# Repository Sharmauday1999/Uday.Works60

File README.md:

# Uday.Works60
 PCB for the FILO60

Features:
- Supports Gasket Mount Boards
- JST connector
- Underglow and in-switch LEDs
- GH60 Layout
- ESD and Over-current protection
- I don't remember the rest :/

It is an Autodesk Eagle Project, I don't have all the footprints handy, but a bit of google should have you set up in no time! I am currently testing a prototype for this but in no way do I guarantee its functionality. This was the biggest PCB project I have ever done and I learned quite alot, feel free to contribute!

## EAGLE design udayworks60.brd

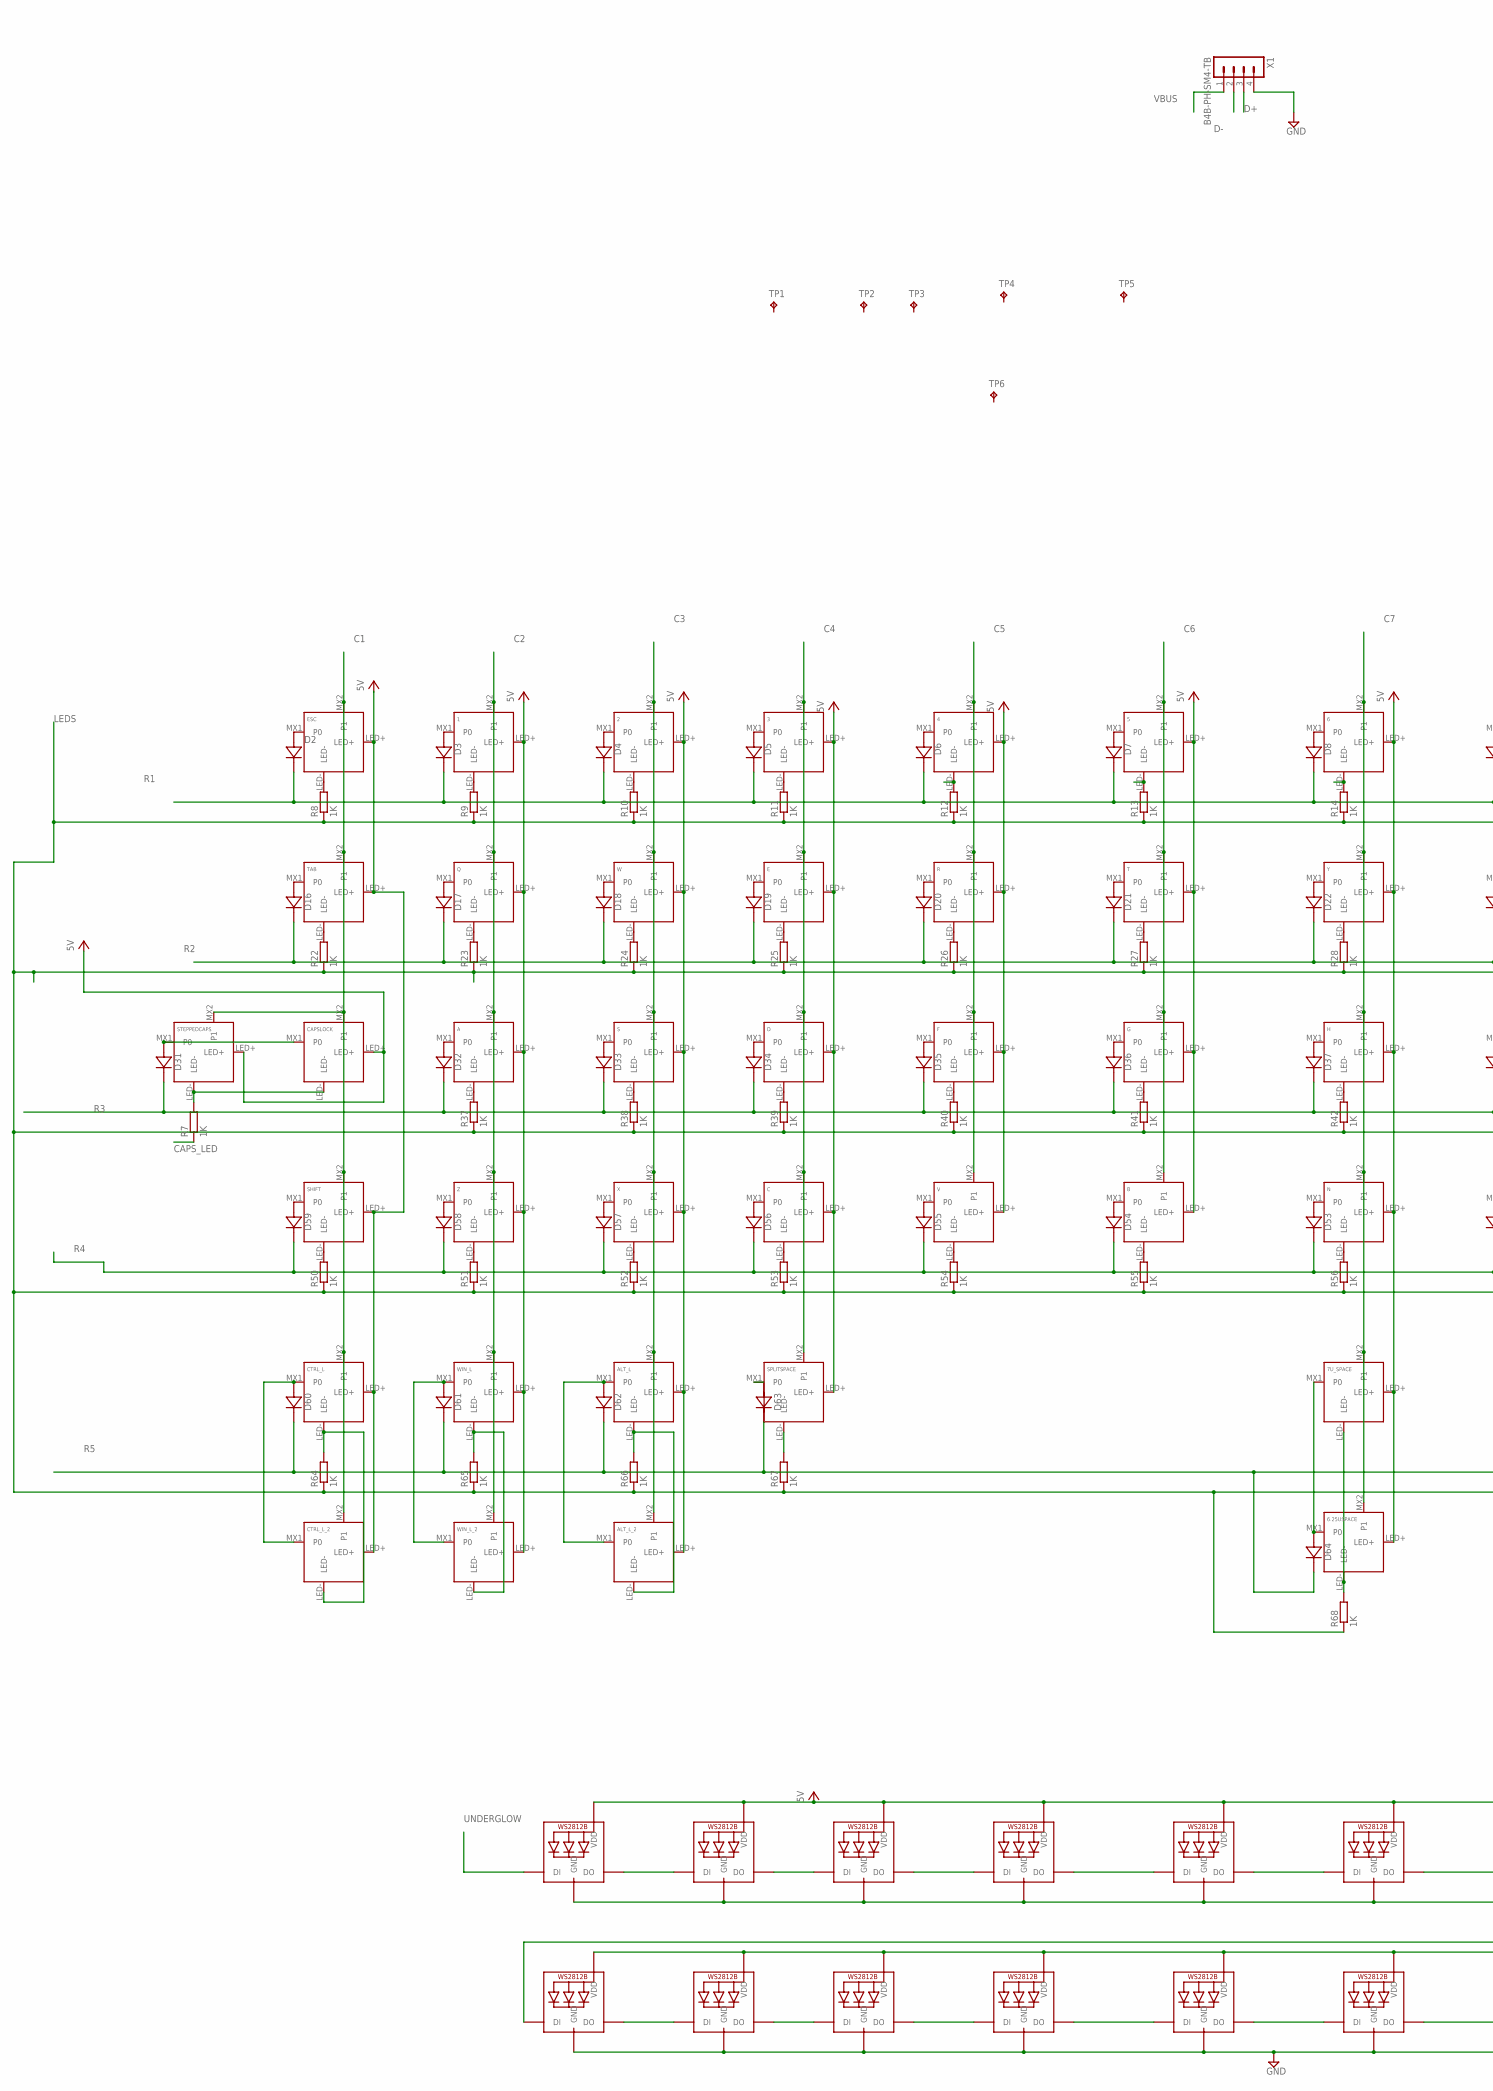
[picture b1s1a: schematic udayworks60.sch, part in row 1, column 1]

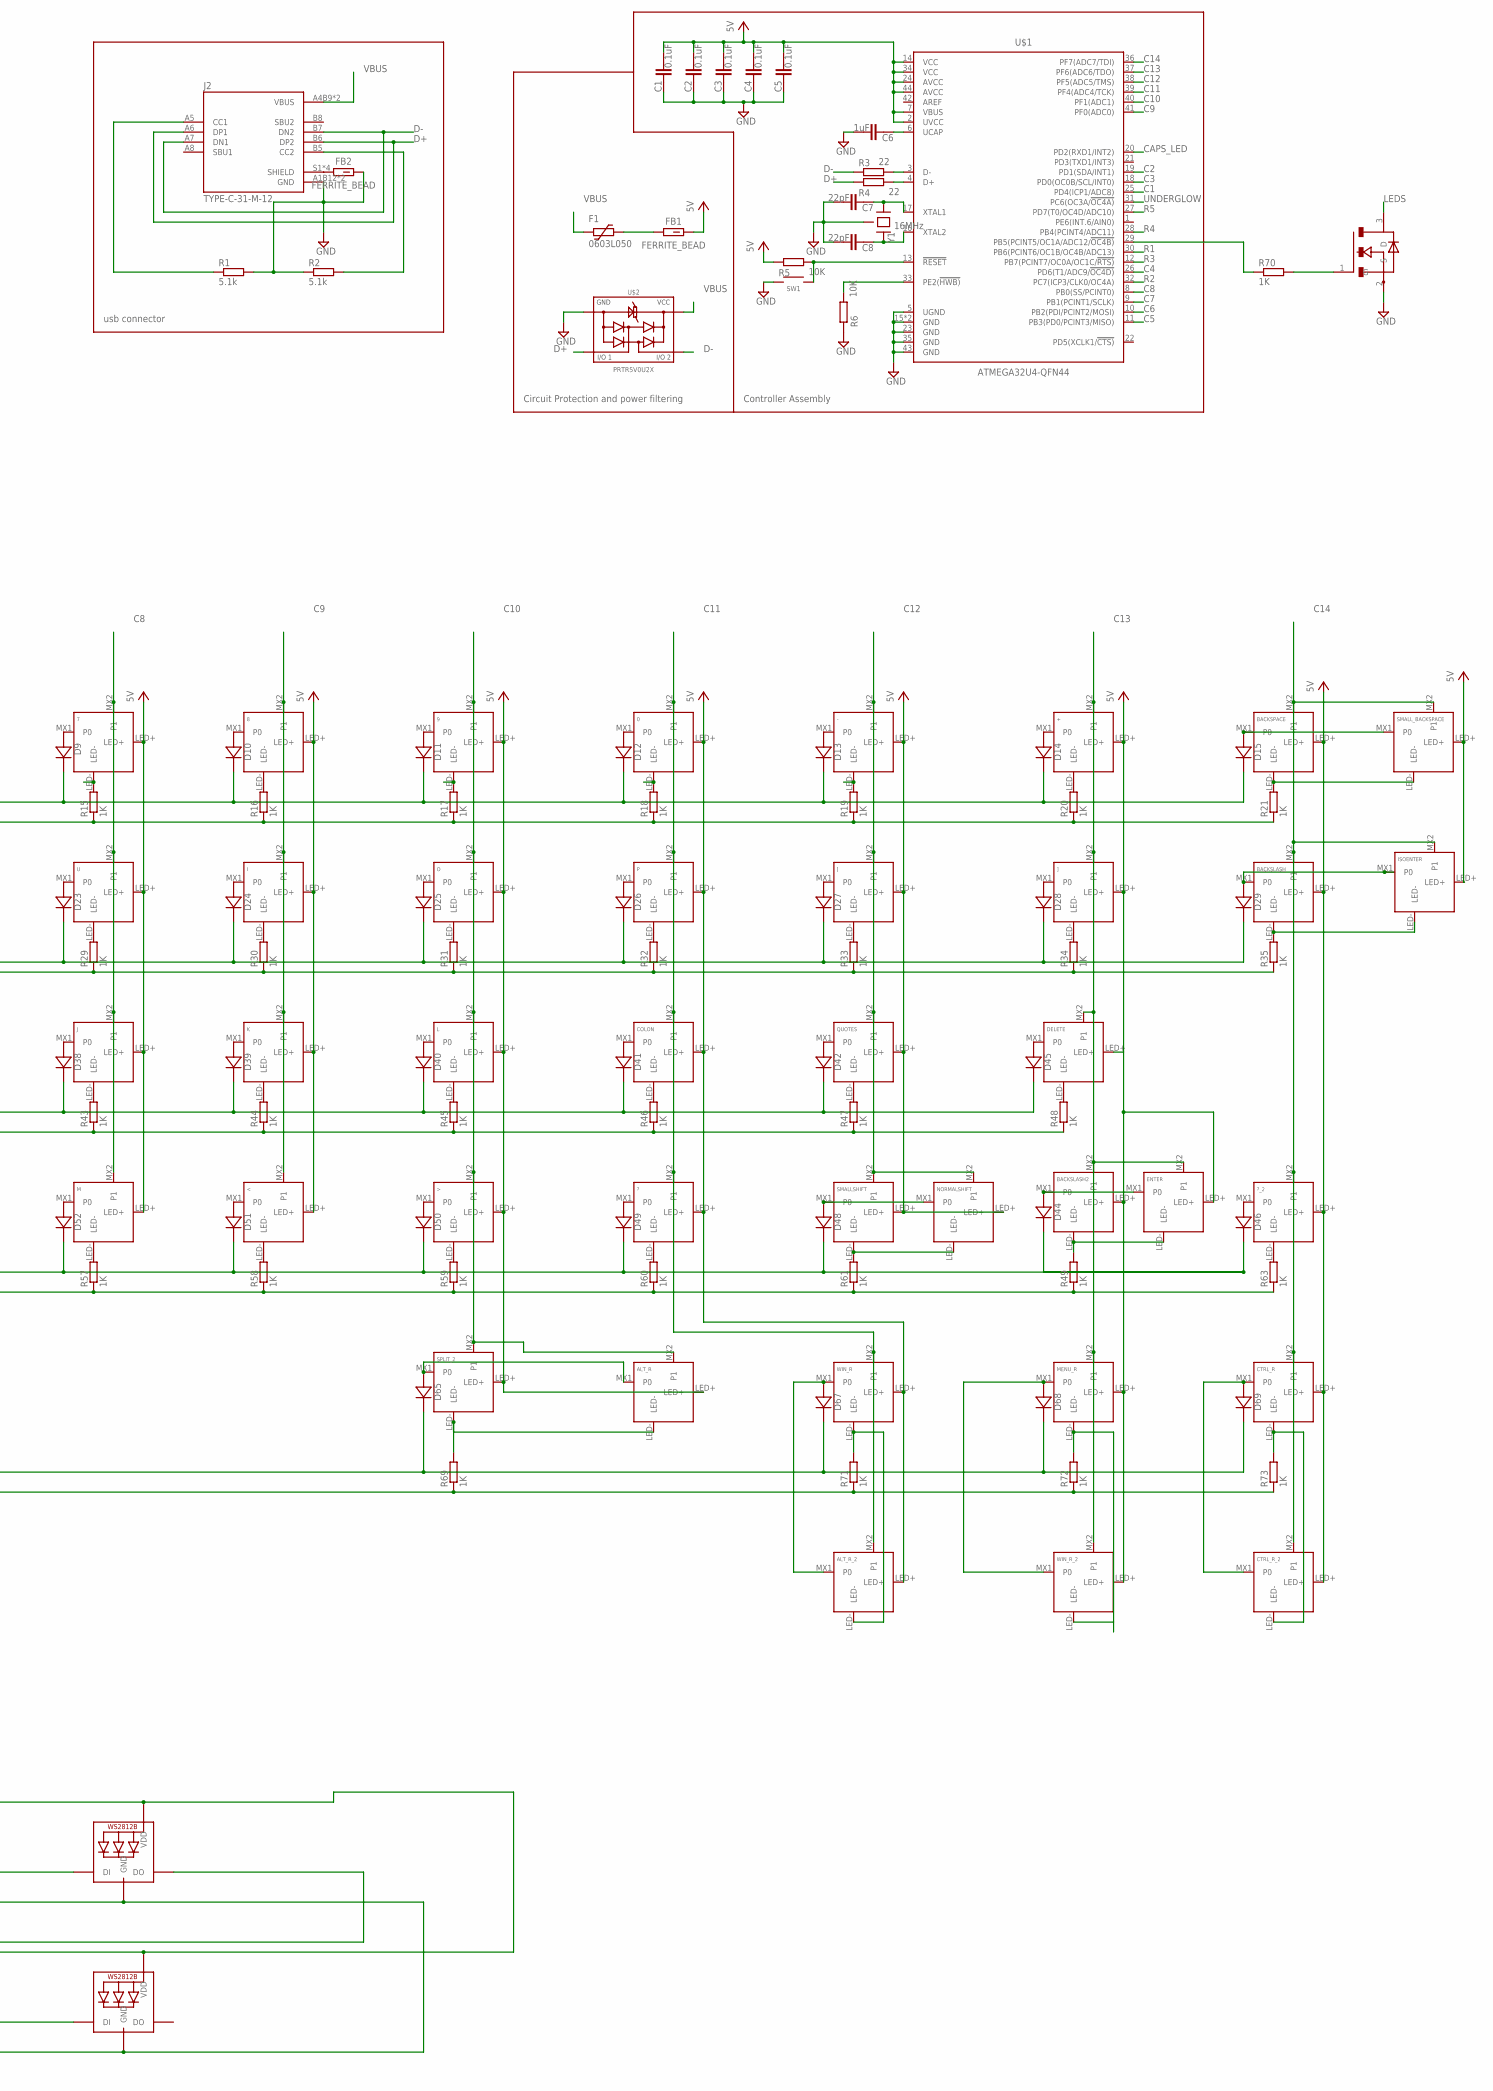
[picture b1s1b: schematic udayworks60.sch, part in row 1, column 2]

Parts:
0, 1, 2, 3, 4, 5, 6, 7, 8, 9: KEYSWITCH-LED-MX-1U-LED; MX-1U-LED
6.25USPACE: KEYSWITCH-LED-MX-6.25U-LED-FLIPPED; MX-6.25U-LED-FLIPPED
7U_SPACE: KEYSWITCH-LED-MX-7U-LED-FLIPPED; MX-7U-LED-FLIPPED
+: KEYSWITCH-LED-MX-1U-LED; MX-1U-LED
-: KEYSWITCH-LED-MX-1U-LED; MX-1U-LED
<: KEYSWITCH-LED-MX-1U-LED; MX-1U-LED
>: KEYSWITCH-LED-MX-1U-LED; MX-1U-LED
?: KEYSWITCH-LED-MX-1U-LED; MX-1U-LED
?_2: KEYSWITCH-LED-MX-1U-LED; MX-1U-LED
A: KEYSWITCH-LED-MX-1U-LED; MX-1U-LED
ALT_L: KEYSWITCH-LED-MX-1U-LED; MX-1U-LED
ALT_L_2: KEYSWITCH-LED-MX-1U-LED; MX-1U-LED
ALT_R: KEYSWITCH-LED-MX-1U-LED; MX-1U-LED
ALT_R_2: KEYSWITCH-LED-MX-1U-LED; MX-1U-LED
B: KEYSWITCH-LED-MX-1U-LED; MX-1U-LED
BACKSLASH, BACKSLASH2: KEYSWITCH-LED-MX-1U-LED; MX-1U-LED
BACKSPACE: KEYSWITCH-LED-MX-2U-LED; MX-2U-LED
C: KEYSWITCH-LED-MX-1U-LED; MX-1U-LED
C1, C2, C3, C4, C5: 0.1uF; C0603
C6: 1uF; C0603
C7, C8: 22pF; C0603
CAPSLOCK: KEYSWITCH-LED-MX-1U-LED; MX-1U-LED
COLON: KEYSWITCH-LED-MX-1U-LED; MX-1U-LED
CTRL_L: KEYSWITCH-LED-MX-1U-LED; MX-1U-LED
CTRL_L_2: KEYSWITCH-LED-MX-1U-LED; MX-1U-LED
CTRL_R: KEYSWITCH-LED-MX-1U-LED; MX-1U-LED
CTRL_R_2: KEYSWITCH-LED-MX-1U-LED; MX-1U-LED
D: KEYSWITCH-LED-MX-1U-LED; MX-1U-LED
D2, D3, D4, D5, D6, D7, D8, D9, D10, D11, D12, D13, D14, D15, D16, D17, D18, D19, D20, D21, D22, D23, D24, D25, D26, D27, D28, D29, D31, D32, D33, D34, D35, D36, D37, D38, D39, D40, D41, D42, D44, D45, D46, D48, D49, D50, D51, D52, D53, D54, D55, D56, D57, D58, D59, D60, D61, D62, D63, D64, D65, D67, D68, D69: DIODE-SOD-123; SOD-123
DELETE: KEYSWITCH-LED-MX-1U-LED; MX-1U-LED
E: KEYSWITCH-LED-MX-1U-LED; MX-1U-LED
ENTER: KEYSWITCH-LED-MX-2U-LED; MX-2U-LED
ESC: KEYSWITCH-LED-MX-1U-LED; MX-1U-LED
F: KEYSWITCH-LED-MX-1U-LED; MX-1U-LED
F1: 0603L050; 0603L
FB1, FB2: FERRITE_BEAD; BEADC1608X95N
FET1: FET-SOT-23-3; SOT-23-3
G: KEYSWITCH-LED-MX-1U-LED; MX-1U-LED
H: KEYSWITCH-LED-MX-1U-LED; MX-1U-LED
I: KEYSWITCH-LED-MX-1U-LED; MX-1U-LED
ISOENTER: KEYSWITCH-LED-MX-2U-LED-FLIPPED-ROTATED; MX-2U-LED-FLIPPED-ROTATED
J: KEYSWITCH-LED-MX-1U-LED; MX-1U-LED
J2: TYPE-C-31-M-12; HRO_TYPE-C-31-M-12
K: KEYSWITCH-LED-MX-1U-LED; MX-1U-LED
L: KEYSWITCH-LED-MX-1U-LED; MX-1U-LED
LED1, LED2, LED3, LED4, LED5, LED6, LED7, LED9, LED10, LED11, LED12, LED13, LED14, LED15: WS2812B3535; LED3535
M: KEYSWITCH-LED-MX-1U-LED; MX-1U-LED
MENU_R: KEYSWITCH-LED-MX-1U-LED; MX-1U-LED
N: KEYSWITCH-LED-MX-1U-LED; MX-1U-LED
NORMALSHIFT: KEYSWITCH-LED-MX-2U-LED; MX-2U-LED
O: KEYSWITCH-LED-MX-1U-LED; MX-1U-LED
P: KEYSWITCH-LED-MX-1U-LED; MX-1U-LED
Q: KEYSWITCH-LED-MX-1U-LED; MX-1U-LED
QUOTES: KEYSWITCH-LED-MX-1U-LED; MX-1U-LED
R: KEYSWITCH-LED-MX-1U-LED; MX-1U-LED
R1, R2: 5.1k; R0603
R3, R4: 22; R0603
R5, R6: 10K; R0603
R7, R8, R9, R10, R11, R12, R13, R14, R15, R16, R17, R18, R19, R20, R21, R22, R23, R24, R25, R26, R27, R28, R29, R30, R31, R32, R33, R34, R35, R37, R38, R39, R40, R41, R42, R43, R44, R45, R46, R47, R48, R49, R50, R51, R52, R53, R54, R55, R56, R57, R58, R59, R60, R61, R63, R64, R65, R66, R67, R68, R69, R70, R71, R72, R73: 1K; R0603
S: KEYSWITCH-LED-MX-1U-LED; MX-1U-LED
SHIFT: KEYSWITCH-LED-MX-2U-LED; MX-2U-LED
SMALLSHIFT: KEYSWITCH-LED-MX-1U-LED; MX-1U-LED
SMALL_BACKSPACE: KEYSWITCH-LED-MX-1U-LED; MX-1U-LED
SPLITSPACE: KEYSWITCH-LED-MX-2U-LED-FLIPPED; MX-2U-LED-FLIPPED
SPLIT_2: KEYSWITCH-LED-MX-2U-LED-FLIPPED; MX-2U-LED-FLIPPED
STEPPEDCAPS: KEYSWITCH-LED-MX-1U-LED; MX-1U-LED
SW1: SWITCH-SMD-EVP-BB2A9B00
T: KEYSWITCH-LED-MX-1U-LED; MX-1U-LED
TAB: KEYSWITCH-LED-MX-1U-LED; MX-1U-LED
TP1, TP2, TP3, TP4, TP5, TP6: TPPAD1-17Y; P1-17Y
U: KEYSWITCH-LED-MX-1U-LED; MX-1U-LED
U$1: ATMEGA32U4-QFN44; QFN-44
U$2: PRTR5V0U2X
V: KEYSWITCH-LED-MX-1U-LED; MX-1U-LED
W: KEYSWITCH-LED-MX-1U-LED; MX-1U-LED
WIN_L: KEYSWITCH-LED-MX-1U-LED; MX-1U-LED
WIN_L_2: KEYSWITCH-LED-MX-1U-LED; MX-1U-LED
WIN_R: KEYSWITCH-LED-MX-1U-LED; MX-1U-LED
WIN_R_2: KEYSWITCH-LED-MX-1U-LED; MX-1U-LED
X: KEYSWITCH-LED-MX-1U-LED; MX-1U-LED
X1: B4B-PH-SM4-TB
Y: KEYSWITCH-LED-MX-1U-LED; MX-1U-LED
Y1: 16MHz; CRYSTAL-3.2X2.5
Z: KEYSWITCH-LED-MX-1U-LED; MX-1U-LED
[: KEYSWITCH-LED-MX-1U-LED; MX-1U-LED
]: KEYSWITCH-LED-MX-1U-LED; MX-1U-LED

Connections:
C1: CAPSLOCK.MX2 (P1), CTRL_L.MX2 (P1), CTRL_L_2.MX2 (P1), ESC.MX2 (P1), SHIFT.MX2 (P1), STEPPEDCAPS.MX2 (P1), TAB.MX2 (P1), U$1.25 (PD4(ICP1/ADC8))
C2: 1.MX2 (P1), A.MX2 (P1), Q.MX2 (P1), U$1.19 (PD1(SDA/INT1)), WIN_L.MX2 (P1), WIN_L_2.MX2 (P1), Z.MX2 (P1)
C3: 2.MX2 (P1), ALT_L.MX2 (P1), ALT_L_2.MX2 (P1), S.MX2 (P1), U$1.18 (PD0(OC0B/SCL/INT0)), W.MX2 (P1), X.MX2 (P1)
C4: 3.MX2 (P1), C.MX2 (P1), D.MX2 (P1), E.MX2 (P1), SPLITSPACE.MX2 (P1), U$1.26 (PD6(T1/ADC9/!OC4D))
C5: 4.MX2 (P1), F.MX2 (P1), R.MX2 (P1), U$1.11 (PB3(PD0/PCINT3/MISO)), V.MX2 (P1)
C6: 5.MX2 (P1), B.MX2 (P1), G.MX2 (P1), T.MX2 (P1), U$1.10 (PB2(PDI/PCINT2/MOSI))
C7: 6.MX2 (P1), 6.25USPACE.MX2 (P1), 7U_SPACE.MX2 (P1), H.MX2 (P1), N.MX2 (P1), U$1.9 (PB1(PCINT1/SCLK)), Y.MX2 (P1)
C8: 7.MX2 (P1), J.MX2 (P1), M.MX2 (P1), U.MX2 (P1), U$1.8 (PB0(SS/PCINT0))
C9: 8.MX2 (P1), <.MX2 (P1), I.MX2 (P1), K.MX2 (P1), U$1.41 (PF0(ADC0))
C10: 9.MX2 (P1), >.MX2 (P1), ALT_R.MX2 (P1), L.MX2 (P1), O.MX2 (P1), SPLIT_2.MX2 (P1), U$1.40 (PF1(ADC1))
C11: 0.MX2 (P1), ?.MX2 (P1), ALT_R_2.MX2 (P1), COLON.MX2 (P1), P.MX2 (P1), U$1.39 (PF4(ADC4/TCK)), WIN_R.MX2 (P1)
C12: -.MX2 (P1), NORMALSHIFT.MX2 (P1), QUOTES.MX2 (P1), SMALLSHIFT.MX2 (P1), U$1.38 (PF5(ADC5/TMS)), [.MX2 (P1)
C13: +.MX2 (P1), BACKSLASH2.MX2 (P1), DELETE.MX2 (P1), ENTER.MX2 (P1), MENU_R.MX2 (P1), U$1.37 (PF6(ADC6/TDO)), WIN_R_2.MX2 (P1), ].MX2 (P1)
C14: ?_2.MX2 (P1), BACKSLASH.MX2 (P1), BACKSPACE.MX2 (P1), CTRL_R.MX2 (P1), CTRL_R_2.MX2 (P1), ISOENTER.MX2 (P1), SMALL_BACKSPACE.MX2 (P1), U$1.36 (PF7(ADC7/TDI))
CAPS_LED: R7.1, U$1.20 (PD2(RXD1/INT2))
D+: J2.A6 (DP1), J2.B6 (DP2), R4.1, U$2.2, X1.3
D-: J2.A7 (DN1), J2.B7 (DN2), R3.1, U$2.3, X1.2
GND: C1.1, C2.1, C3.1, C4.1, C5.1, C6.2, C7.2, C8.2, FB2.2, FET1.2 (S), J2.A1B12 (GND), J2.B1A12 (GND), LED1.4 (GND), LED2.4 (GND), LED3.4 (GND), LED4.4 (GND), LED5.4 (GND), LED6.4 (GND), LED7.4 (GND), LED9.4 (GND), LED10.4 (GND), LED11.4 (GND), LED12.4 (GND), LED13.4 (GND), LED14.4 (GND), LED15.4 (GND), R1.2, R2.1, R6.1, SW1.A@1 (1), SW1.A@2 (1), U$1.5 (UGND), U$1.15 (GND), U$1.23 (GND), U$1.35 (GND), U$1.43 (GND), U$1.TAB (GND), U$2.1, X1.4, Y1.2 (GND), Y1.4 (GND)
LEDS: FET1.3 (D), R8.1, R9.1, R10.1, R11.1, R12.1, R13.1, R14.1, R15.1, R16.1, R17.1, R18.1, R19.1, R20.1, R21.1, R22.1, R23.1, R24.1, R25.1, R26.1, R27.1, R28.1, R29.1, R30.1, R31.1, R32.1, R33.1, R34.1, R35.1, R37.1, R38.1, R39.1, R40.1, R41.1, R42.1, R43.1, R44.1, R45.1, R46.1, R47.1, R48.1, R49.1, R50.1, R51.1, R52.1, R53.1, R54.1, R55.1, R56.1, R57.1, R58.1, R59.1, R60.1, R61.1, R63.1, R64.1, R65.1, R66.1, R67.1, R68.1, R69.1, R71.1, R72.1, R73.1
unnamed: D2.A, ESC.MX1 (P0)
unnamed: 1.MX1 (P0), D3.A
unnamed: 2.MX1 (P0), D4.A
unnamed: 3.MX1 (P0), D5.A
unnamed: 4.MX1 (P0), D6.A
unnamed: 5.MX1 (P0), D7.A
unnamed: 6.MX1 (P0), D8.A
unnamed: 7.MX1 (P0), D9.A
unnamed: 8.MX1 (P0), D10.A
unnamed: 9.MX1 (P0), D11.A
unnamed: 0.MX1 (P0), D12.A
unnamed: -.MX1 (P0), D13.A
unnamed: +.MX1 (P0), D14.A
unnamed: D16.A, TAB.MX1 (P0)
unnamed: D17.A, Q.MX1 (P0)
unnamed: D18.A, W.MX1 (P0)
unnamed: D19.A, E.MX1 (P0)
unnamed: D20.A, R.MX1 (P0)
unnamed: D21.A, T.MX1 (P0)
unnamed: D22.A, Y.MX1 (P0)
unnamed: D23.A, U.MX1 (P0)
unnamed: D24.A, I.MX1 (P0)
unnamed: D25.A, O.MX1 (P0)
unnamed: D26.A, P.MX1 (P0)
unnamed: D27.A, [.MX1 (P0)
unnamed: D28.A, ].MX1 (P0)
unnamed: CAPSLOCK.MX1 (P0), D31.A, STEPPEDCAPS.MX1 (P0)
unnamed: A.MX1 (P0), D32.A
unnamed: D33.A, S.MX1 (P0)
unnamed: D.MX1 (P0), D34.A
unnamed: D35.A, F.MX1 (P0)
unnamed: D36.A, G.MX1 (P0)
unnamed: D37.A, H.MX1 (P0)
unnamed: D38.A, J.MX1 (P0)
unnamed: D39.A, K.MX1 (P0)
unnamed: D40.A, L.MX1 (P0)
unnamed: COLON.MX1 (P0), D41.A
unnamed: D42.A, QUOTES.MX1 (P0)
unnamed: D58.A, Z.MX1 (P0)
unnamed: D57.A, X.MX1 (P0)
unnamed: C.MX1 (P0), D56.A
unnamed: D55.A, V.MX1 (P0)
unnamed: B.MX1 (P0), D54.A
unnamed: D53.A, N.MX1 (P0)
unnamed: D52.A, M.MX1 (P0)
unnamed: <.MX1 (P0), D51.A
unnamed: >.MX1 (P0), D50.A
unnamed: ?.MX1 (P0), D49.A
unnamed: D48.A, NORMALSHIFT.MX1 (P0), SMALLSHIFT.MX1 (P0)
unnamed: CTRL_L.MX1 (P0), CTRL_L_2.MX1 (P0), D60.A
unnamed: D61.A, WIN_L.MX1 (P0), WIN_L_2.MX1 (P0)
unnamed: ALT_L.MX1 (P0), ALT_L_2.MX1 (P0), D62.A
unnamed: CAPSLOCK.LED-, R7.2, STEPPEDCAPS.LED-
unnamed: ALT_R_2.MX1 (P0), D67.A, WIN_R.MX1 (P0)
unnamed: D68.A, MENU_R.MX1 (P0), WIN_R_2.MX1 (P0)
unnamed: CTRL_R.MX1 (P0), CTRL_R_2.MX1 (P0), D69.A
unnamed: BACKSLASH2.MX1 (P0), D44.A, ENTER.MX1 (P0)
unnamed: DELETE.LED-, R48.2
unnamed: ?_2.MX1 (P0), D46.A
unnamed: D59.A, SHIFT.MX1 (P0)
unnamed: 6.25USPACE.MX1 (P0), 7U_SPACE.MX1 (P0), D64.A
unnamed: BACKSPACE.MX1 (P0), D15.A, SMALL_BACKSPACE.MX1 (P0)
unnamed: BACKSLASH.MX1 (P0), D29.A, ISOENTER.MX1 (P0)
unnamed: D63.A, SPLITSPACE.MX1 (P0)
unnamed: ALT_R.MX1 (P0), D65.A, SPLIT_2.MX1 (P0)
unnamed: C6.1, U$1.6 (UCAP)
unnamed: R3.2, U$1.3 (D-)
unnamed: R4.2, U$1.4 (D+)
unnamed: Q.LED-, R23.2
unnamed: C7.1, U$1.17 (XTAL1), Y1.1
unnamed: FB2.1, J2.S1 (SHIELD), J2.S2 (SHIELD), J2.S3 (SHIELD), J2.S4 (SHIELD)
unnamed: C8.1, U$1.16 (XTAL2), Y1.3 (2)
unnamed: R5.2, SW1.B@3 (2), SW1.B@4 (2), U$1.13 (!RESET)
unnamed: R6.2, U$1.33 (PE2(!HWB))
unnamed: F1.1, FB1.1
unnamed: D45.A, DELETE.MX1 (P0)
unnamed: 4.LED-, R12.2
unnamed: 5.LED-, R13.2
unnamed: 6.LED-, R14.2
unnamed: 7.LED-, R15.2
unnamed: 9.LED-, R17.2
unnamed: R70.1, U$1.29 (PB5(PCINT5/OC1A/ADC12/!OC4B))
unnamed: 0.LED-, R18.2
unnamed: -.LED-, R19.2
unnamed: FET1.1 (G), R70.2
unnamed: ESC.LED-, R8.2
unnamed: 1.LED-, R9.2
unnamed: A.LED-, R37.2
unnamed: R22.2, TAB.LED-
unnamed: R24.2, W.LED-
unnamed: E.LED-, R25.2
unnamed: R.LED-, R26.2
unnamed: 2.LED-, R10.2
unnamed: 3.LED-, R11.2
unnamed: 8.LED-, R16.2
unnamed: +.LED-, R20.2
unnamed: BACKSPACE.LED-, R21.2, SMALL_BACKSPACE.LED-
unnamed: R27.2, T.LED-
unnamed: R28.2, Y.LED-
unnamed: R29.2, U.LED-
unnamed: I.LED-, R30.2
unnamed: O.LED-, R31.2
unnamed: P.LED-, R32.2
unnamed: R33.2, [.LED-
unnamed: R34.2, ].LED-
unnamed: BACKSLASH.LED-, ISOENTER.LED-, R35.2
unnamed: R38.2, S.LED-
unnamed: ?_2.LED-, R63.2
unnamed: NORMALSHIFT.LED-, R61.2, SMALLSHIFT.LED-
unnamed: ?.LED-, R60.2
unnamed: >.LED-, R59.2
unnamed: <.LED-, R58.2
unnamed: M.LED-, R57.2
unnamed: N.LED-, R56.2
unnamed: B.LED-, R55.2
unnamed: R54.2, V.LED-
unnamed: C.LED-, R53.2
unnamed: R52.2, X.LED-
unnamed: R51.2, Z.LED-
unnamed: R50.2, SHIFT.LED-
unnamed: D.LED-, R39.2
unnamed: CTRL_R.LED-, CTRL_R_2.LED-, R73.2
unnamed: 6.25USPACE.LED-, 7U_SPACE.LED-, R68.2
unnamed: ALT_R.LED-, R69.2, SPLIT_2.LED-
unnamed: ALT_R_2.LED-, R71.2, WIN_R.LED-
unnamed: MENU_R.LED-, R72.2, WIN_R_2.LED-
unnamed: F.LED-, R40.2
unnamed: G.LED-, R41.2
unnamed: R67.2, SPLITSPACE.LED-
unnamed: ALT_L.LED-, ALT_L_2.LED-, R66.2
unnamed: R65.2, WIN_L.LED-, WIN_L_2.LED-
unnamed: LED9.3 (DO), LED10.1 (DI)
unnamed: H.LED-, R42.2
unnamed: J.LED-, R43.2
unnamed: K.LED-, R44.2
unnamed: L.LED-, R45.2
unnamed: COLON.LED-, R46.2
unnamed: QUOTES.LED-, R47.2
unnamed: BACKSLASH2.LED-, ENTER.LED-, R49.2
unnamed: CTRL_L.LED-, CTRL_L_2.LED-, R64.2
unnamed: J2.A5 (CC1), R1.1
unnamed: J2.B5 (CC2), R2.2
unnamed: LED10.3 (DO), LED11.1 (DI)
unnamed: LED11.3 (DO), LED12.1 (DI)
unnamed: LED12.3 (DO), LED13.1 (DI)
unnamed: LED1.3 (DO), LED2.1 (DI)
unnamed: LED2.3 (DO), LED3.1 (DI)
unnamed: LED3.3 (DO), LED4.1 (DI)
unnamed: LED4.3 (DO), LED5.1 (DI)
unnamed: LED5.3 (DO), LED6.1 (DI)
unnamed: LED6.3 (DO), LED7.1 (DI)
unnamed: LED7.3 (DO), LED9.1 (DI)
unnamed: LED13.3 (DO), LED14.1 (DI)
unnamed: LED14.3 (DO), LED15.1 (DI)
R1: D2.C, D3.C, D4.C, D5.C, D6.C, D7.C, D8.C, D9.C, D10.C, D11.C, D12.C, D13.C, D14.C, D15.C, U$1.30 (PB6(PCINT6/OC1B/OC4B/ADC13))
R2: D16.C, D17.C, D18.C, D19.C, D20.C, D21.C, D22.C, D23.C, D24.C, D25.C, D26.C, D27.C, D28.C, D29.C, U$1.32 (PC7(ICP3/CLK0/OC4A))
R3: D31.C, D32.C, D33.C, D34.C, D35.C, D36.C, D37.C, D38.C, D39.C, D40.C, D41.C, D42.C, D45.C, U$1.12 (PB7(PCINT7/OC0A/OC1C/!RTS))
R4: D44.C, D46.C, D48.C, D49.C, D50.C, D51.C, D52.C, D53.C, D54.C, D55.C, D56.C, D57.C, D58.C, D59.C, U$1.28 (PB4(PCINT4/ADC11))
R5: D60.C, D61.C, D62.C, D63.C, D64.C, D65.C, D67.C, D68.C, D69.C, U$1.27 (PD7(T0/OC4D/ADC10))
UNDERGLOW: LED1.1 (DI), U$1.31 (PC6(OC3A/!OC4A))
VBUS: F1.2, J2.A4B9 (VBUS), J2.B4A9 (VBUS), U$2.4, X1.1
VCC: 0.LED+, 1.LED+, 2.LED+, 3.LED+, 4.LED+, 5.LED+, 6.LED+, 6.25USPACE.LED+, 7.LED+, 7U_SPACE.LED+, 8.LED+, 9.LED+, +.LED+, -.LED+, <.LED+, >.LED+, ?.LED+, ?_2.LED+, A.LED+, ALT_L.LED+, ALT_L_2.LED+, ALT_R.LED+, ALT_R_2.LED+, B.LED+, BACKSLASH.LED+, BACKSLASH2.LED+, BACKSPACE.LED+, C.LED+, C1.2, C2.2, C3.2, C4.2, C5.2, CAPSLOCK.LED+, COLON.LED+, CTRL_L.LED+, CTRL_L_2.LED+, CTRL_R.LED+, CTRL_R_2.LED+, D.LED+, DELETE.LED+, E.LED+, ENTER.LED+, ESC.LED+, F.LED+, FB1.2, G.LED+, H.LED+, I.LED+, ISOENTER.LED+, J.LED+, K.LED+, L.LED+, LED1.2 (VDD), LED2.2 (VDD), LED3.2 (VDD), LED4.2 (VDD), LED5.2 (VDD), LED6.2 (VDD), LED7.2 (VDD), LED9.2 (VDD), LED10.2 (VDD), LED11.2 (VDD), LED12.2 (VDD), LED13.2 (VDD), LED14.2 (VDD), LED15.2 (VDD), M.LED+, MENU_R.LED+, N.LED+, NORMALSHIFT.LED+, O.LED+, P.LED+, Q.LED+, QUOTES.LED+, R.LED+, R5.1, S.LED+, SHIFT.LED+, SMALLSHIFT.LED+, SMALL_BACKSPACE.LED+, SPLITSPACE.LED+, SPLIT_2.LED+, STEPPEDCAPS.LED+, T.LED+, TAB.LED+, U.LED+, U$1.2 (UVCC), U$1.7 (VBUS), U$1.14 (VCC), U$1.24 (AVCC), U$1.34 (VCC), U$1.44 (AVCC), V.LED+, W.LED+, WIN_L.LED+, WIN_L_2.LED+, WIN_R.LED+, WIN_R_2.LED+, X.LED+, Y.LED+, Z.LED+, [.LED+, ].LED+

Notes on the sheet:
usb connector
Controller Assembly
Circuit Protection and power filtering

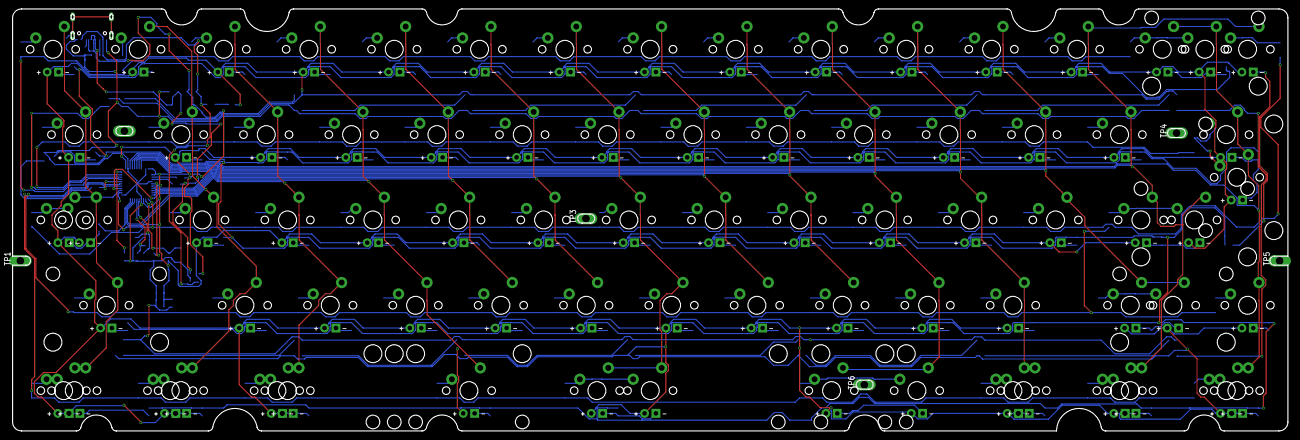
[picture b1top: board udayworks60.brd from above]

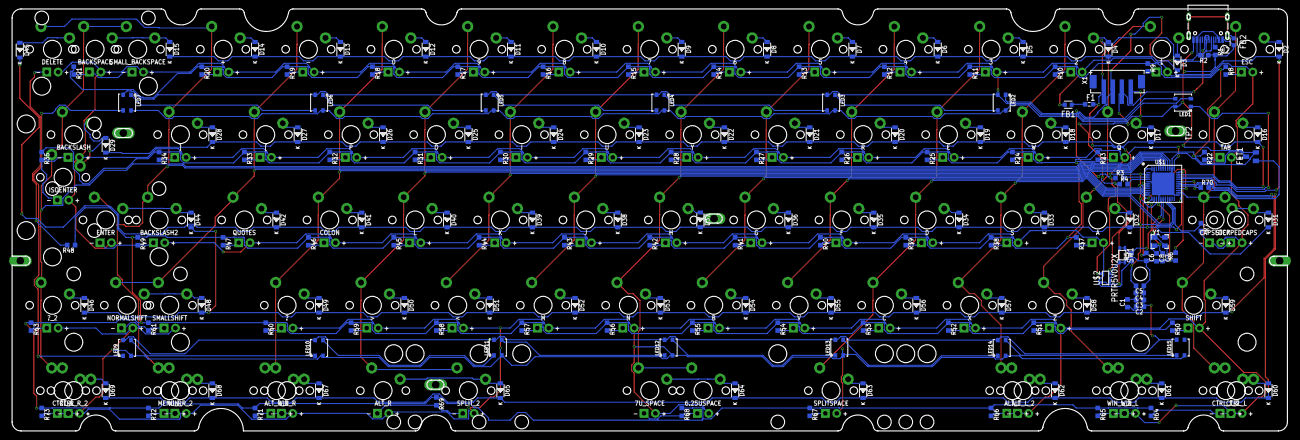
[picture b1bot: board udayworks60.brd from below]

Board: 2 copper layers, 284.7 x 94.2 mm, 250 parts (168 on the bottom side), 181 nets.

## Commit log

2020-12-18 Image added
2020-12-18 Create LICENSE
